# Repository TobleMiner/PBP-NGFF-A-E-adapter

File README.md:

Pinebook Pro M.2 WiFi adapter
=============================

#### Overview

The M.2 A/E key adapter enables the use of M.2 WiFi cards in the Pinebook Pro ARM laptop.  

This adapter was designed as a replacement for the available [NVMe M.2 (M-key) adapter](https://store.pine64.org/?product=pinebook-pro-m-2ngff-nvme-ssd-interface-adapter).  
It uses the same flat flex cable, mounting screws and mounting position. 

USB is not present on the PBP FFC and needs to be connected manually if required.  
Test points for D- and D+ are present on the PCB.  
Most WiFi+Bluetooth combo cards use USB for Bluetooth, but the PBPs internal UART HCI bluetooth adapter can still be used, even after disabling the SDIO WiFi kernel module.  

#### Tested cards

All testing was done using Manjaro ARM, kernel 5.6 and 5.7-rc1. 

Card | Test result
--- | ---
Intel AX200NGW | Works very well, stable, requires additional firmware.
Atheros QCA6174A | Kernel panic at boot, not recommended.

Pull requests with additional test results welcome. 

#### Bill of materials

The board offers an additional footprint for a switch-mode regulator to guarantee a stable 3.3V supply for the M.2 card. 
In our testing this wasn't required and can be left unpopulated. The only required components are the 2 connectors and either a 0805 SMD fuse or 0 ohm resistor at F1.

The PCB should be manufactured as a **1.0mm thick** FR4 board. 

[Interactive BOM](https://tobleminer.github.io/PBP-NGFF-A-E-adapter/ibom.html)

| Design. | Description | Part No.           | Links  |
| ----- |:-------:|:-------------:| -----:|
| J1 | FFC conn. | Hirose FH26W-35S-0.3SHW | [Datasheet](https://www.mouser.de/datasheet/2/185/FH26_CL0580-2410-2-60_2d-1614872.pdf) \| [Mouser](https://www.mouser.de/ProductDetail/hirose-electric/fh26w-35s-03shw60/?qs=vcbW%252b4%252bSTIqfjIQXayKHZQ==&countrycode=DE&currencycode=EUR) |
| J2 | M.2 E-key | Amphenol MDT275E02001 | [Datasheet](https://www.mouser.de/datasheet/2/18/Amphenol_CMDTXXXXXX001-4-1157232.pdf) \| [Mouser](https://www.mouser.de/ProductDetail/fci-amphenol/mdt275e02001/?qs=lrCDz5EUXIYT3rGac7uMeg==&countrycode=DE&currencycode=EUR)  |
| - | Dual-band MHF4 antenna | Laird EMN2449R1S-8MHF4 | [Mouser](https://www.mouser.de/ProductDetail/laird-connectivity/emn2449r1s-8mhf4/?qs=EU6FO9ffTwfxyryKAvXAaQ==&countrycode=DE&currencycode=EUR)

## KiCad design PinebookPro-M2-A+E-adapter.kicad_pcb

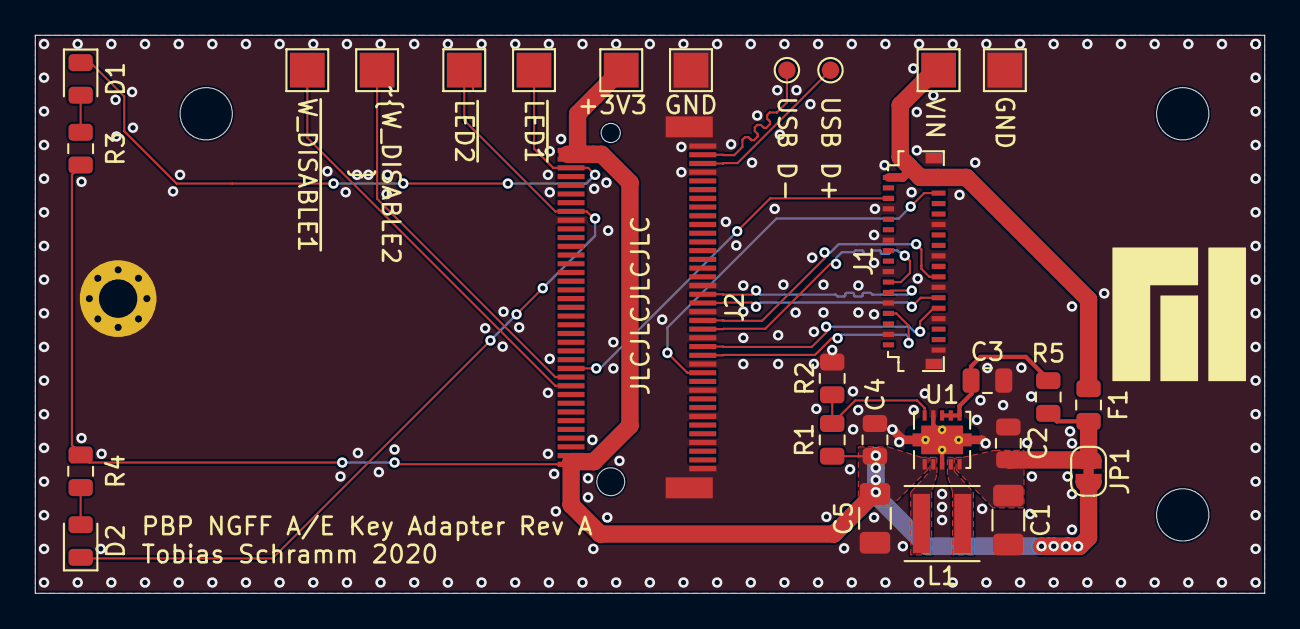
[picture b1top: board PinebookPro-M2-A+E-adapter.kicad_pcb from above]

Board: 2 copper layers, 70.5 x 32.0 mm, 29 parts (0 on the bottom side), 24 nets.

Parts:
C1, C5: DNP; C_1206_3216Metric
C2, C4: 10 µF; C_0805_2012Metric
C3: 100 nF; C_0805_2012Metric
D1, D2: LED; LED_0805_2012Metric
F1: 2 A; Fuse_0805_2012Metric
H1: MountingHole_Pad; MountingHole_2.2mm_M2_Pad_Via
J1: Conn_01x35_MountingPin; Hirose_FH26-35S-0.3SH_2x35-1MP_P0.30mm_Horizontal
J2: M.2-NGFF-A+E-Key; MDTXXXXXX001
JP1: SolderJumper_2_Bridged; SolderJumper-2_P1.3mm_Bridged_RoundedPad1.0x1.5mm
L1: 2.2 µH; L_Coilcraft_XxL4020
R1: 0 R; R_0805_2012Metric
R2: DNP; R_0805_2012Metric
R3, R4: 330 R; R_0805_2012Metric
R5: 100 R; R_0805_2012Metric
TP1, TP2: TestPoint; TestPoint_Pad_D1.0mm
TP3, TP4, TP5, TP6, TP7, TP8, TP9, TP10: TestPoint; TestPoint_Pad_2.0x2.0mm
U1: TPS63001; Texas_DRC0010J_ThermalVias

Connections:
+3V0: F1.2, J1.33, J1.34, J1.35, TP8.1
+3V3: C4.1, C5.1, J2.2, J2.4, J2.72, J2.74, JP1.2, R1.1, R3.1, R4.1, TP7.1, U1.1
/REFCLK+: J1.9, J2.47
/REFCLK-: J1.8, J2.49
/RX+: J1.15, J2.41
/RX-: J1.14, J2.43
/TX+: J1.12, J2.35
/TX-: J1.11, J2.37
/USB_D+: J2.3, TP2.1
/USB_D-: J2.5, TP1.1
/~CLKREQ: J1.31, J2.53
/~LED1: D1.1, J2.6, TP5.1
/~LED2: D2.1, J2.16, TP6.1
/~PERST: J1.30, J2.52
/~W_DISABLE1: J2.56, TP3.1
/~W_DISABLE2: J2.54, TP4.1
GND: C1.2, C2.2, C3.2, C4.2, C5.2, H1.1, J1.1, J1.4, J1.7, J1.10, J1.13, J1.16, J1.19, J1.22, J1.25, J1.28, J1.MP, J2.1, J2.7, J2.18, J2.33, J2.39, J2.45, J2.51, J2.57, J2.63, J2.69, J2.75, J2.MP, R2.2, TP9.1, TP10.1, U1.3, U1.9, U1.11
unnamed: C1.1, C2.1, F1.1, JP1.1, R5.1, U1.5
unnamed: C3.1, R5.2, U1.6, U1.7, U1.8
unnamed: D1.2, R3.2
unnamed: D2.2, R4.2
unnamed: L1.1, U1.4
unnamed: L1.2, U1.2
unnamed: R1.2, R2.1, U1.10

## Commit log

2020-03-28 Add GND testpoints
2020-03-28 Add VINA strapping resistor
2020-03-31 Rev A
2020-04-24 Cleanup
2020-04-24 Add bom
2020-04-24 Add additional documentation
2020-04-24 Add photo of board
2020-04-24 Add recommended antenna to BOM
